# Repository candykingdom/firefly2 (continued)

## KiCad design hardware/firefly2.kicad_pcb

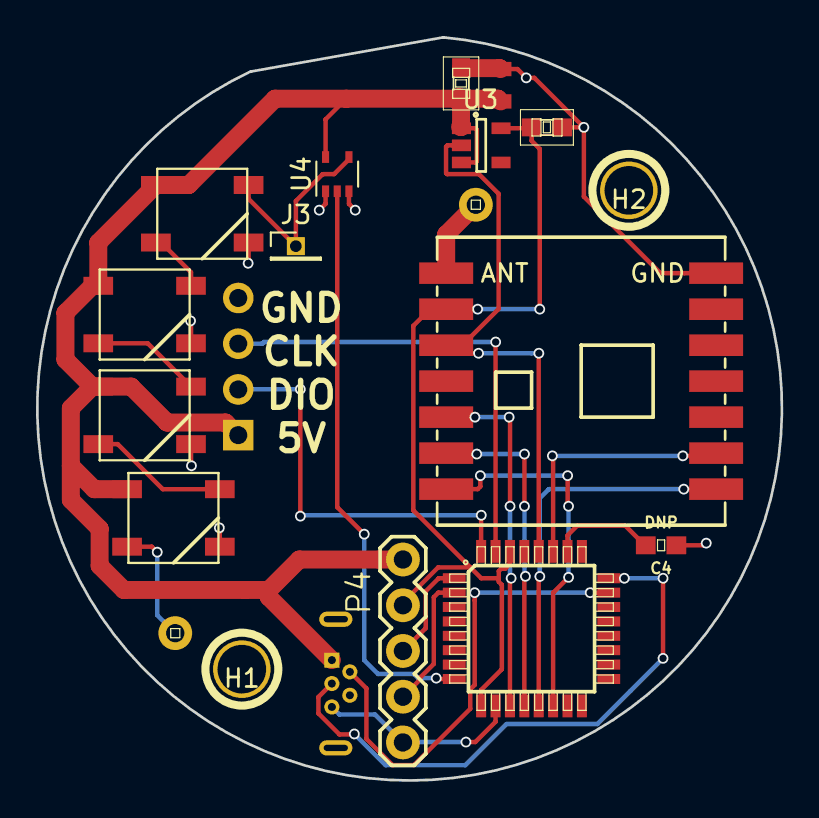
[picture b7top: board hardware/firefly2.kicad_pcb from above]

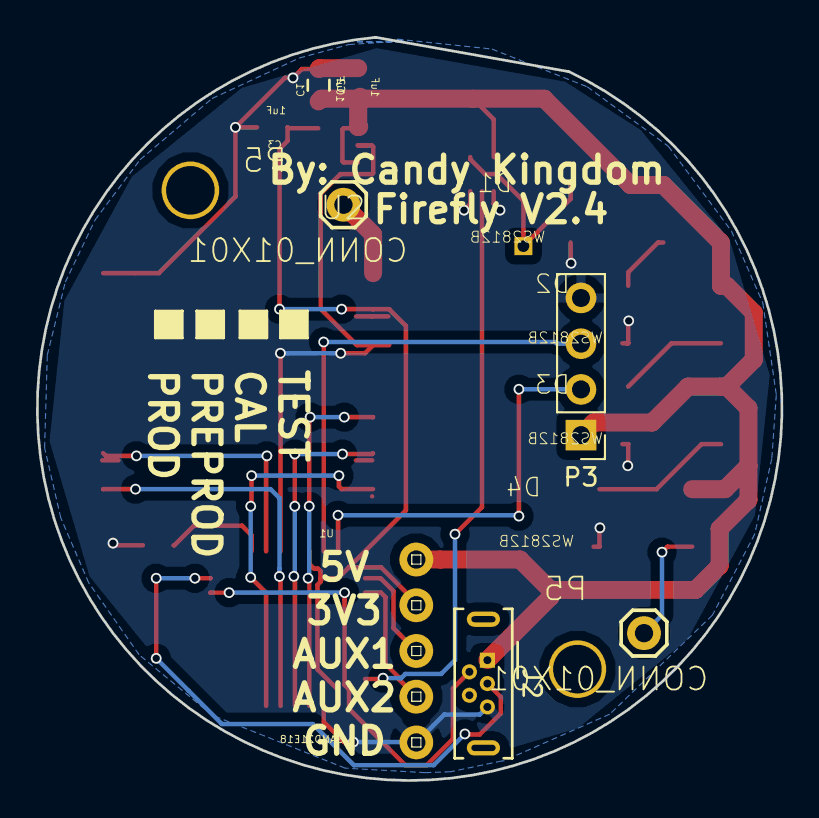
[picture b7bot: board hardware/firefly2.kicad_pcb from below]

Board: 2 copper layers, 41.4 x 41.3 mm, 20 parts (3 on the bottom side), 22 nets.

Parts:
C1: 10uF; 0805
C2, C3: 1uF; 0603
C4: DNP; 0603
D1, D2, D3, D4: WS2812B
H1, H2: hole; hole-m2.5
J2: 614105150721; USB_Micro-B_Wuerth-614105150721_Vertical
J3: CONN_01X01; Pin_Header_Straight_1x01_Pitch1.27mm
P3: CONN_01X04; Pin_Header_Straight_1x04_Pitch2.54mm
P4: CONN_01X05; 1X05
P5, P5#2: CONN_01X01; 1X01
U1: SAMD21E18; TQFP32-08
U2: RFM69CW
U3: MIC5504; SOT-23-5
U4: 74LVC1G125; SOT-353_SC-70-5

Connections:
+3V3: C3.2, P4.2, U1.9, U1.30, U2.2, U3.5
+5V: C1.2, C2.2, D1.1, D2.1, D3.1, D4.1, J2.1, P3.1, P4.1, U3.1, U3.3, U4.5
ANTENNA: P5#2.1, U2.1
ARM_SWCLK: P3.3, U1.31
ARM_SWDIO: P3.2, U1.32
AUX1: P4.3, U1.1
AUX2: P4.4, U1.2
GND: C1.1, C2.1, C3.1, C4.1, D1.3, D2.3, D3.3, D4.3, J2.5, P3.4, P4.5, U1.10, U1.28, U2.3, U2.14, U3.2, U4.1, U4.3
LED_EXTERNAL: D4.2, P5.1
LED_INTERNAL: U1.8, U4.2
unnamed: C4.2, U1.26
unnamed: D1.2, D2.4
unnamed: D1.4, J3.1, U4.4
unnamed: D2.2, D3.4
unnamed: D3.2, D4.4
RADIO_DIO0: U1.27, U2.9
RADIO_MISO: U1.13, U2.8
RADIO_MOSI: U1.11, U2.5
RADIO_NSS: U1.14, U2.7
RADIO_SCK: U1.12, U2.6
USB_D+: J2.3, U1.24
USB_D-: J2.2, U1.23

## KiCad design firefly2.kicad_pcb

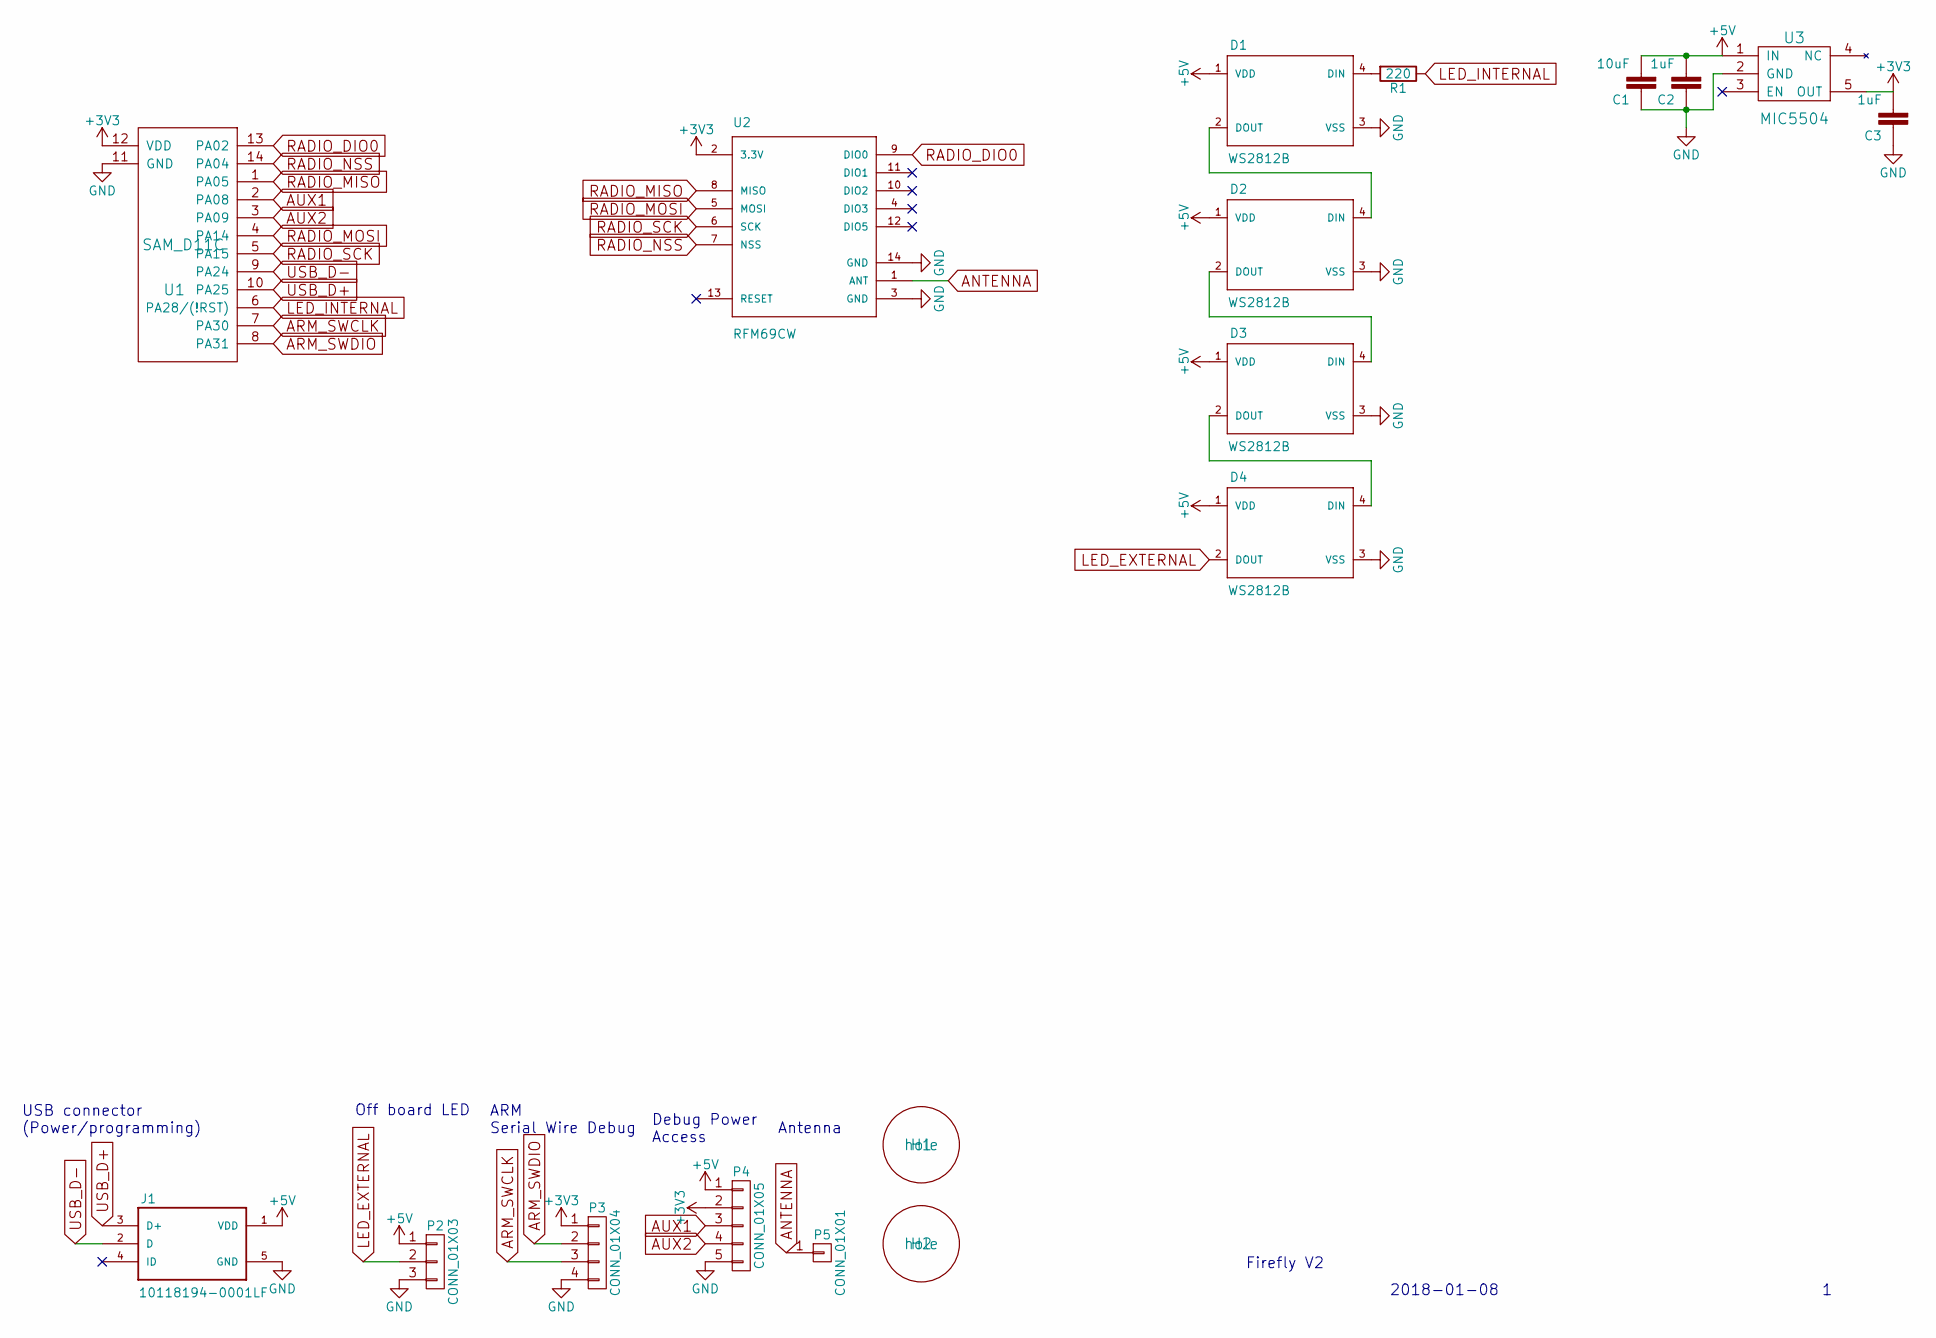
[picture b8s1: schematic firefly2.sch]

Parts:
C1: 10uF; 0805
C2, C3: 1uF; 0603
D1, D2, D3, D4: WS2812B
H1, H2: hole; hole-m2.5
J1: 10118194-0001LF; FRAMATOME_10118194-0001LF
P2: CONN_01X03; 1X03
P3: CONN_01X04; 1X04
P4: CONN_01X05; 1X05
P5: CONN_01X01; 1X01
R1: 220; 0603
U1: SAM_D11C; SOIC-14_N
U2: RFM69CW; RFM69CW-XXXS2
U3: MIC5504; SOT-23-5

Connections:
+3V3: C3.2, P3.1, P4.2, U1.12 (VDD), U2.2 (3.3V), U3.5 (OUT)
+5V: C1.2, C2.2, D1.1 (VDD), D2.1 (VDD), D3.1 (VDD), D4.1 (VDD), J1.1 (VDD), P2.1, P4.1, U3.1 (IN)
ANTENNA: P5.1, U2.1 (ANT)
ARM_SWCLK: P3.3, U1.7 (PA30)
ARM_SWDIO: P3.2, U1.8 (PA31)
AUX1: P4.3, U1.2 (PA08)
AUX2: P4.4, U1.3 (PA09)
GND: C1.1, C2.1, C3.1, D1.3 (VSS), D2.3 (VSS), D3.3 (VSS), D4.3 (VSS), J1.5 (GND), P2.3, P3.4, P4.5, U1.11 (GND), U2.3 (GND), U2.14 (GND), U3.2 (GND)
LED_EXTERNAL: D4.2 (DOUT), P2.2
LED_INTERNAL: R1.1, U1.6 (PA28/(!RST))
unnamed: D1.2 (DOUT), D2.4 (DIN)
unnamed: D1.4 (DIN), R1.2
unnamed: D2.2 (DOUT), D3.4 (DIN)
unnamed: D3.2 (DOUT), D4.4 (DIN)
RADIO_DIO0: U1.13 (PA02), U2.9 (DIO0)
RADIO_MISO: U1.1 (PA05), U2.8 (MISO)
RADIO_MOSI: U1.4 (PA14), U2.5 (MOSI)
RADIO_NSS: U1.14 (PA04), U2.7 (NSS)
RADIO_SCK: U1.5 (PA15), U2.6 (SCK)
USB_D+: J1.3 (D+), U1.10 (PA25)
USB_D-: J1.2 (D), U1.9 (PA24)

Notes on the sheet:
Firefly V2
2018-01-08
USB connector (Power/programming)
Off board LED
ARM Serial Wire Debug
Debug Power Access
Antenna

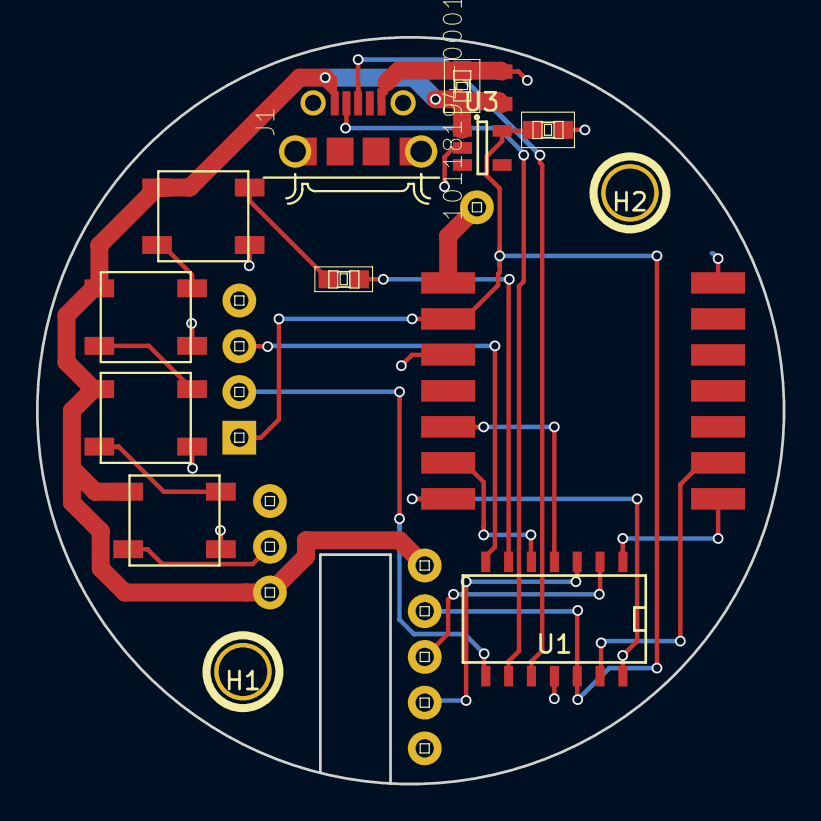
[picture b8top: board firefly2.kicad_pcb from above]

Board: 2 copper layers, 41.5 x 41.5 mm, 18 parts (0 on the bottom side), 21 nets.

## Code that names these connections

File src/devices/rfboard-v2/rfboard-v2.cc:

#include <Arduino.h>
#include <FastLED.h>
#include <FlashStorage_STM32.h>

#include <DeviceDescription.hpp>
#include <Devices.hpp>
#include <StripDescription.hpp>
#include <vector>

#include "../../arduino/FastLedManager.hpp"
#include "../../arduino/RadioHeadRadio.hpp"
#include "../../generic/NetworkManager.hpp"
#include "../../generic/RadioStateMachine.hpp"

// The onboard addressable LED, which then feeds the external LED connector
constexpr int kPinLedInternal = PA4; 
constexpr int kPinRedLed = PB1;
constexpr int kPinSw1 = PB6;
constexpr int kPinSw2 = PB7;

constexpr int kPin5vDivided = PA0;
constexpr int kPinCc1 = PA1;
constexpr int kPinCc2 = PB2;
constexpr int kPinVibrationSensor = PA8;

RadioHeadRadio *radio = new RadioHeadRadio();
NetworkManager network_manager(radio);
RadioStateMachine state_machine(&network_manager);
FastLedManager *led_manager;

void setup() {
  pinMode(kPinLedInternal, OUTPUT);
  pinMode(kPinRedLed, OUTPUT);
  pinMode(kPinSw1, INPUT_PULLUP);
  pinMode(kPinSw2, INPUT_PULLUP);

  pinMode(kPin5vDivided, INPUT_ANALOG);
  pinMode(kPinCc1, INPUT_ANALOG);
  pinMode(kPinCc2, INPUT_ANALOG);
  pinMode(kPinVibrationSensor, INPUT);

  // TODO: support reading the device description from flash
  led_manager = new FastLedManager(Devices::current, &state_machine);

  if (!radio->Begin()) {
    led_manager->FatalErrorAnimation();
  }

  // NOTE: can check if we watchdog rebooted by checking REG_PM_RCAUSE
  // See https://github.com/gjt211/SAMD21-Reset-Cause
  led_manager->PlayStartupAnimation();

  // TODO: configure and enable the watchdog
}

void loop() {
  digitalWrite(kPinRedLed, (millis() / 100) % 2);
  state_machine.Tick();
  led_manager->RunEffect();

  // Test code - remove after bringup
  if (false) {
    digitalWrite(kPinRedLed, digitalRead(kPinSw1));
  }

  if (false) {
    digitalWrite(kPinRedLed, digitalRead(kPinSw2));
  }

  if (false) {
    digitalWrite(kPinRedLed, digitalRead(kPinVibrationSensor));
  }
}

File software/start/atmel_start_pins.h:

/*
 * Code generated from Atmel Start.
 *
 * This file will be overwritten when reconfiguring your Atmel Start project.
 * Please copy examples or other code you want to keep to a separate file
 * to avoid losing it when reconfiguring.
 */
#ifndef ATMEL_START_PINS_H_INCLUDED
#define ATMEL_START_PINS_H_INCLUDED

#include <hal_gpio.h>

// SAMD11 has 8 pin functions

#define GPIO_PIN_FUNCTION_A 0
#define GPIO_PIN_FUNCTION_B 1
#define GPIO_PIN_FUNCTION_C 2
#define GPIO_PIN_FUNCTION_D 3
#define GPIO_PIN_FUNCTION_E 4
#define GPIO_PIN_FUNCTION_F 5
#define GPIO_PIN_FUNCTION_G 6
#define GPIO_PIN_FUNCTION_H 7

#define PA05 GPIO(GPIO_PORTA, 5)
#define PA14 GPIO(GPIO_PORTA, 14)
#define PA15 GPIO(GPIO_PORTA, 15)
#define PA24 GPIO(GPIO_PORTA, 24)
#define PA25 GPIO(GPIO_PORTA, 25)

#endif // ATMEL_START_PINS_H_INCLUDED

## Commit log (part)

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2022-05-22 Cleanup DeviceDescription constructor
2022-05-23 Fix tests
    I honestly don't know how they were passing before...
2022-05-24 Add clang-format
    This adds clang-format rules as well as a GitHub actions linter.
2022-05-24 Format all the files!
2022-05-24 Remove old format
2022-05-24 Add clang-format (#15)
    * Add clang-format
    This adds clang-format rules as well as a GitHub actions linter.
    * Fix name of action
    * Format all the files!
    * We missed a bunch of files
    * Remove old format
2022-05-25 Add a startup animation (#16)
    This 1s animation lights up every light on the device. It makes it easy
    to see if the board is configured to use the device it is plugged into.
2022-05-25 Fix tests
    Remove toString, it was more trouble than it was worth.
2022-05-26 Redefine DeviceDescription in terms of flags (#17)
    * Redefine DeviceDescription in terms of flags
    This allows us to branch on semantic flags as well as print out the
    device description on startup.
    * Fix tests
    Remove toString, it was more trouble than it was worth.
    * Use std::list for DeviceFlags
2022-05-26 Add polar interpolation of Perlin noise
    This allows us to render Perlin noise across circular devices correctly.
2022-05-26 Update Rainbow Bumps effect for circular devices
    With keeping the math the same for linear devices we end up with a cool,
    three dots effect on circular devices.
2022-05-27 Update Rainbow Bumps effect for circular devices (#21)
    With keeping the math the same for linear devices we end up with a cool,
    three dots effect on circular devices.
2022-05-27 Use tiny flag in effects (#18)
    Rework some of the flags that were determining device size using LED
    count.
2022-05-28 Move Math.hpp into Math.cpp
2022-05-28 Add Mirrored flag
    This will allow us to have chained strips that display the same pattern
    on each, regardless of orientation.
    Also add helper function to mirror indicies.
2022-05-29 Make MirrorIndex more robust
2022-05-29 Add Mirrored flag (#22)
    * Add Mirrored flag
    This will allow us to have chained strips that display the same pattern
    on each, regardless of orientation.
    Also add helper function to mirror indicies.
    * Revert test code
    * Make MirrorIndex more robust
2022-05-29 Tweak all effects to use all flags
    Adhere to the flags when the behavior makes sense for the effect.
2022-05-29 The_great_snake_case_refactor
    Rename all variables, parameters, and member-variables to snake_case.
2022-05-29 Move Effects into //lib/effect
    This is the start of normalizing our repo structure to follow PIO
    standards.
2022-05-29 Fix the linter
2022-05-29 Move all libraries into lib
    Everything except for //software/devices and GTest code has been
    moved under //lib.
2022-05-29 Explicitly include API and arduino libraries
    Refernce to Types by relative path rather than global (pio isn't playing
    nicely with global imports)
2022-05-29 Remove unnecessary directories
2022-05-31 Add DeviceDescription for the rainbow cloak (#28)
2022-05-31 Move all the other libs too
2022-06-04 Introduce strip description
    This is a different abstraction from the device description where one
    device can run multiple strips in parallel. Each strip can get its own
    set of flags.
    Now the device description only describes the hardware before the LED
    strip.
    Also added FastLED max power draw and refresh rate.
2022-06-04 Add test
2022-06-04 Remove stray test filter
2022-06-04 I love when `random()` has side-effects from other tests.
2022-06-04 Add Pride effect
    Just in time for this month I guess.
2022-06-04 Move device code into //lib/device (#32)
2022-06-05 Refactor //software to //src
    This matches what PlatformIO expects. Also cleaned up some of the
    platformio.ini definitions.
2022-06-05 Refactor //software to //src (#33)
    * Refactor //software to //src
    This matches what PlatformIO expects. Also cleaned up some of the
    platformio.ini definitions.
    * Remove unnecessary lines
2022-06-09 Don't set board LED (#34)
    The board LED only serves as a pass-through.
    Added DeviceDescription::GetLedCount() to reduce copy-paste.
2022-06-20 Ignore KiCAD temporary files
2022-06-24 Enable ASAN for tests.
    Fix all detected memory leaks.
2022-06-24 First pass at fancy-node schematic
2022-06-30 fancy-node v1.0
2022-07-01 Update magnet connector with correct dimensions
2022-07-03 Enable the undefined behavior sanitizer for tests (#38)
    Also split tests into small and large.
2022-07-14 Start adding fancy-node code (broken)
2022-07-17 Add fancy-node to CI
2022-07-18 Fix 128 LED bug
    Turns out the startup animation would just go into a loop if the total
    LED strip had 128 or more LEDs on it. This was fixed by using the
    correct integer type in the animation.
2022-07-18 Tune effect frequency by type
    Made some effects less frequent based on user feedback. Note this
    feedback is anecdotal but these decisions are from third parties (I'm
    bias myself so I tried not to influence opinions).
    Moved SimpleBlinkEffect(300) to the strobes because it's "not fun" when
    it's your primary light source.
2022-07-24 fancy-node v1.1:
    - Actually connect VBATT_DIV to micro
    - Add resistor on DIO0 line to protect against firmware errors
    - Move WS2812b line to SPI2, to not conflict with the radio SPI in case
    we want to use the SPI with DMA to output the NRZ
2022-07-29 Port main code to fancy-node
2022-08-13 Add bike DeviceDescription (#43)
    Add a device description for Will's bike
2022-08-14 Add Jacket device types
2022-08-14 Correct WS2812_PIN in pio (#44)
2022-08-17 Start work on the controller
    Add FastLedControllerManager to handle the Firefly controller's LEDs.
    Attempt to display an effect on the top-most row of LEDs.
2022-08-18 Fix formatting
2022-08-18 Tune effect frequency by type (#41)
    Made some effects less frequent based on user feedback. Note this
    feedback is anecdotal but these decisions are from third parties (I'm
    bias myself so I tried not to influence opinions).
    Moved SimpleBlinkEffect(300) to the strobes because it's "not fun" when
    it's your primary light source.
2022-08-19 Refactor LED manager methods to take constant references for RGB params
2022-08-19 Pause rebroadcasting if many rebroadcasts are seen recently.
    Now that we could have a lot more boards, I'm concerned that every node
    rebroadcasting could cause issues. This will hopefully avoid that
    congestion.
2022-10-02 Update rfboard to KiCAD 6
2022-11-06 Restructure CMake project.
    This moves CMakeLists.txt and the tests to the top-level directory.
2022-11-06 Add basic simulator
2023-01-07 Add some more device descriptions (#49)
2023-02-06 Add documentation on programming the fancy-node over USB
2023-02-26 Update controller designs to KiCAD v7
2023-02-26 Revert "Ignore CMake build dir"
    This reverts commit fcd5f2b83f14511768abf727230dd4cbe0727dbd. It's not
    needed, since we've moved to the new CMake structure at the top level.
2023-02-26 Update Github action versions
2023-02-26 Fix some compiler warnings.
    - Don't define the UNUSED macro for STM32F1xx, where it's already
    defined
    - Don't return in noreturn functions
2023-03-02 Use raw objects, not pointers, for Firefly classes.
    This is less error prone, since it relies on the natural object
    lifecycle.
2023-03-02 Document why palettes() is a function, and cleanup node
2023-03-02 Revert "Create codeql.yml"
    This reverts commit 28c614cc2d3d6c28faa553b62fbc92d9e96f542a.
2023-03-05 Update RadioHead to 1.120 and pin FastLED versions
    This updates FastLED deps to remove spammy pragma messages.
2023-03-05 Use DeviceDescription references instead of pointers
2023-03-06 Display color palettes across multiple LEDs
2023-03-06 Use filtering for the analog button inputs
2023-03-06 Run linter
2023-03-07 Add clarifying comments in the controller
2023-03-07 Format analog-button.cpp
2023-04-01 Update fancy-node to KiCAD v7 and fix charging LED
2023-04-04 Controller PCB version 1.1
2023-04-05 Cost optimizations for controller v1.1
    This consolidates some of the resistors values to reduce the number of
    BOM line items.
2023-04-07 Update controller PCB v1.1:
    - Switch to in-stock light sensor
    - Move power switch to top of board, so it's populated by JLC
2023-04-19 Default packet id and length to 0
2023-04-19 Fix memory leak in RadioStateIntegrationTest
2023-04-19 Fix memory leaks in tests
2023-04-19 Mark most constructors as explicit.
    This is recommended by Google C++ style: https://abseil.io/tips/142
    Without this, C++ produces unexpected (to the programmer) behavior.
2023-04-19 Add slope detection to button reading in the controller.
    This fixes the issue where pressing button 1 would trigger button 2.
2023-04-19 Use button LEDs in effect mode
2023-04-19 Implement controller palette mode
2023-04-19 Use the mode switch in software
2023-04-19 Implement controller color mode
2023-04-22 Migrate controller to stm32g070 for board v1.1
2023-04-22 Clear nBOOT_SEL in fancy-node init
2023-04-22 Format
2023-04-26 Update schematic for fancy-node v1.2, and first pass at layout:
    - Smaller buttons
    - Smaller PCB antenna
    - Smaller power switch
    - Move to CH340X, hook up BOOT0 to it
    - Smaller overall board size (47mm x 33mm, vs 60mm x 37mm)
    - Add JST 1.25 for batteries
2023-04-30 Generate fab files for fancy-node v1.2
2023-05-01 DFM tweaks for fancy-node v1.2
2023-05-05 Add proof-of-concept for fancy-node EEPROM emulation
2023-05-05 fancy-node cleanup:
    - Increase brightness of low battery LED, and actually show it
    - Add delay to main loop, to avoid stomping on LEDs before writing out
2023-05-05 Add modes to read and write device description to flash
2023-05-05 Add documentation for saving device descriptions to flash
2023-05-05 Fix low-battery detection on fancy node.
    Previously, the math for calculating the levels was incorrect. This
    fixes those calculations, and improves the logic.
2023-05-05 Add type and length asserts to RadioPacket read functions
2023-05-05 Set the microcontroller family for stm32loader.
    This hides the warning about setting this flag, and displays the flash
    size.
2023-05-05 Clean up radio code.
    This migrates from C arrays to std::array, and marks some member
    functions as const.
2023-05-10 Unignore xml and csv files
2023-05-13 Round traces and generate production files for ring-50mm
2023-05-16 Extract common battery stuff into a library
2023-05-28 Add todo to change controller battery button
2023-05-28 Add serial and jump to bootloader function to controller
2023-05-29 Add dimensions to the ring schematics
2023-05-29 Increase fancy-node battery voltage cutoff voltage again, based on real-world testing
2023-05-31 Use RTC bootloader trick in fancy-node v1.2
2023-06-03 Fix bootloader logic to enter application on initial power on.
2023-06-03 Display saturation in color config mode
2023-06-03 Make button lights more consistent.
    During config, this makes buttons blink when those buttons advance to
    the next step.
2023-06-03 Add support for changing the colors in direct color mode.
2023-06-03 Move palette mode code to its own files
2023-06-03 Add support for carousels to color mode
2023-06-03 Save and load color and palette config to fram
2023-06-04 Tune startup animation
    Display a hue cycle on the last LED of a strip so you know you got the
    number right.
2023-06-07 Update bootloader programmer
    Include the new image file.
2023-06-07 Default node to get device description from header, not flash
2023-08-13 Add LED matrix panels to device types
2023-08-16 Inrease watchdog timeout period
2024-05-24 Remove Arduino implementation of __throw_bad_alloc and __throw_length_error.
    They're now implemented in the standard library.
2024-05-24 Lint
2025-03-14 Update rfboard to KiCAD v8
2025-03-17 rfboard v2.0: schematic updates
2025-05-02 rfboard: add LC filter for radio
2025-05-07 Claude md update
2025-05-08 MacOS support for platformio
